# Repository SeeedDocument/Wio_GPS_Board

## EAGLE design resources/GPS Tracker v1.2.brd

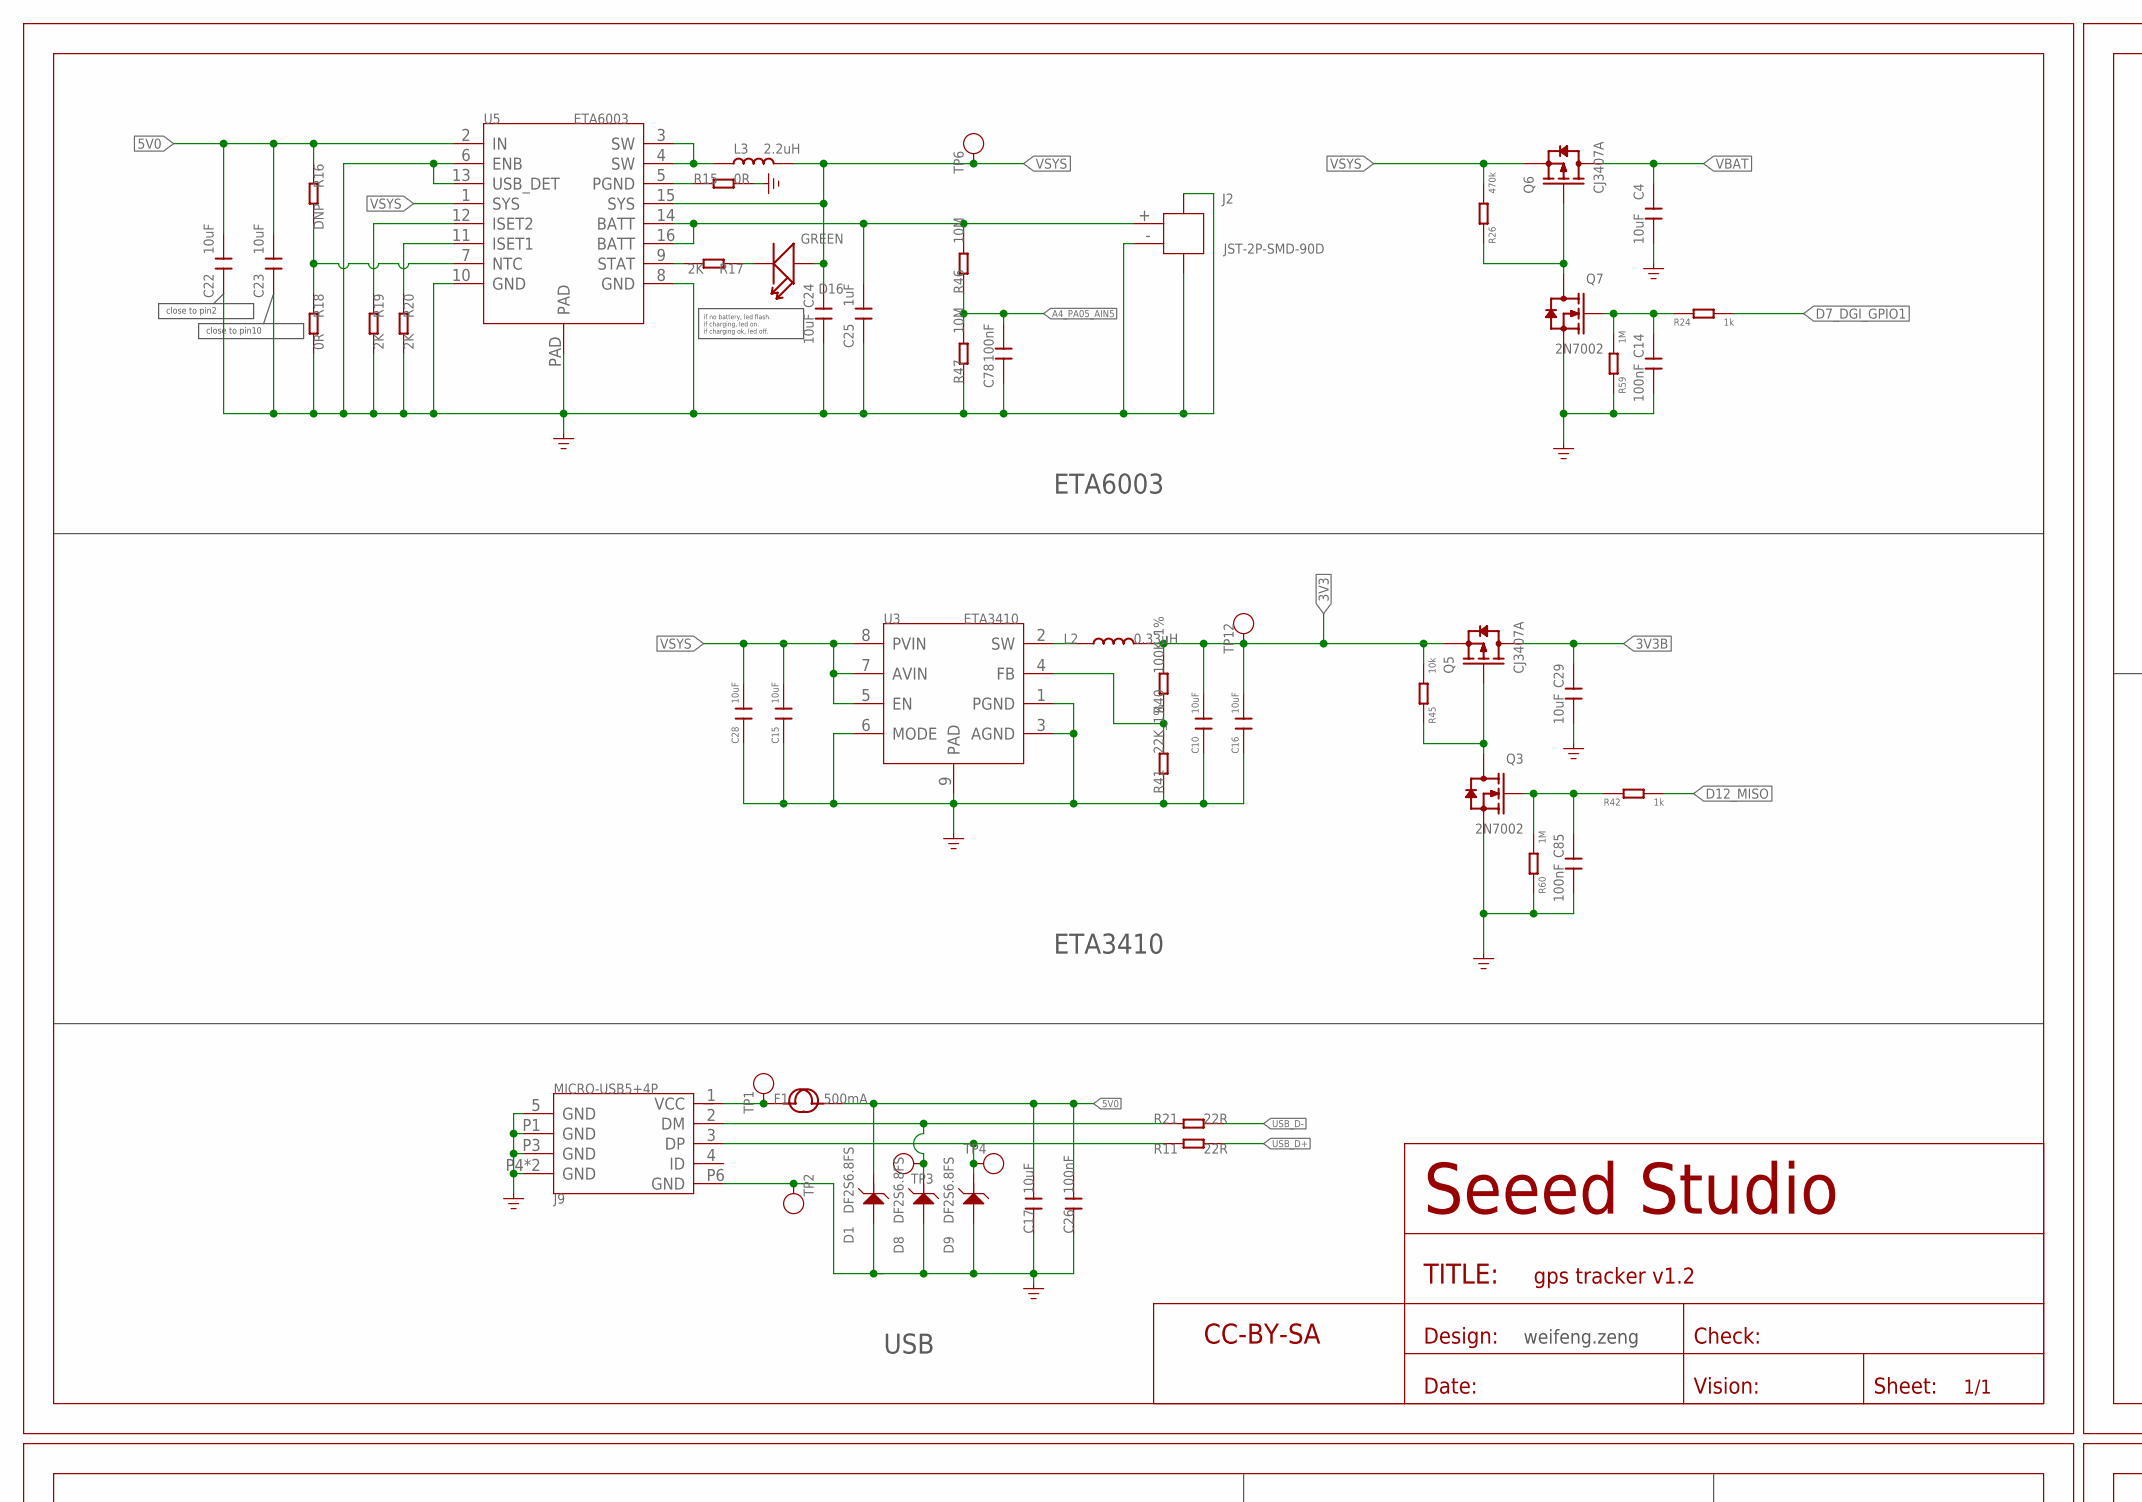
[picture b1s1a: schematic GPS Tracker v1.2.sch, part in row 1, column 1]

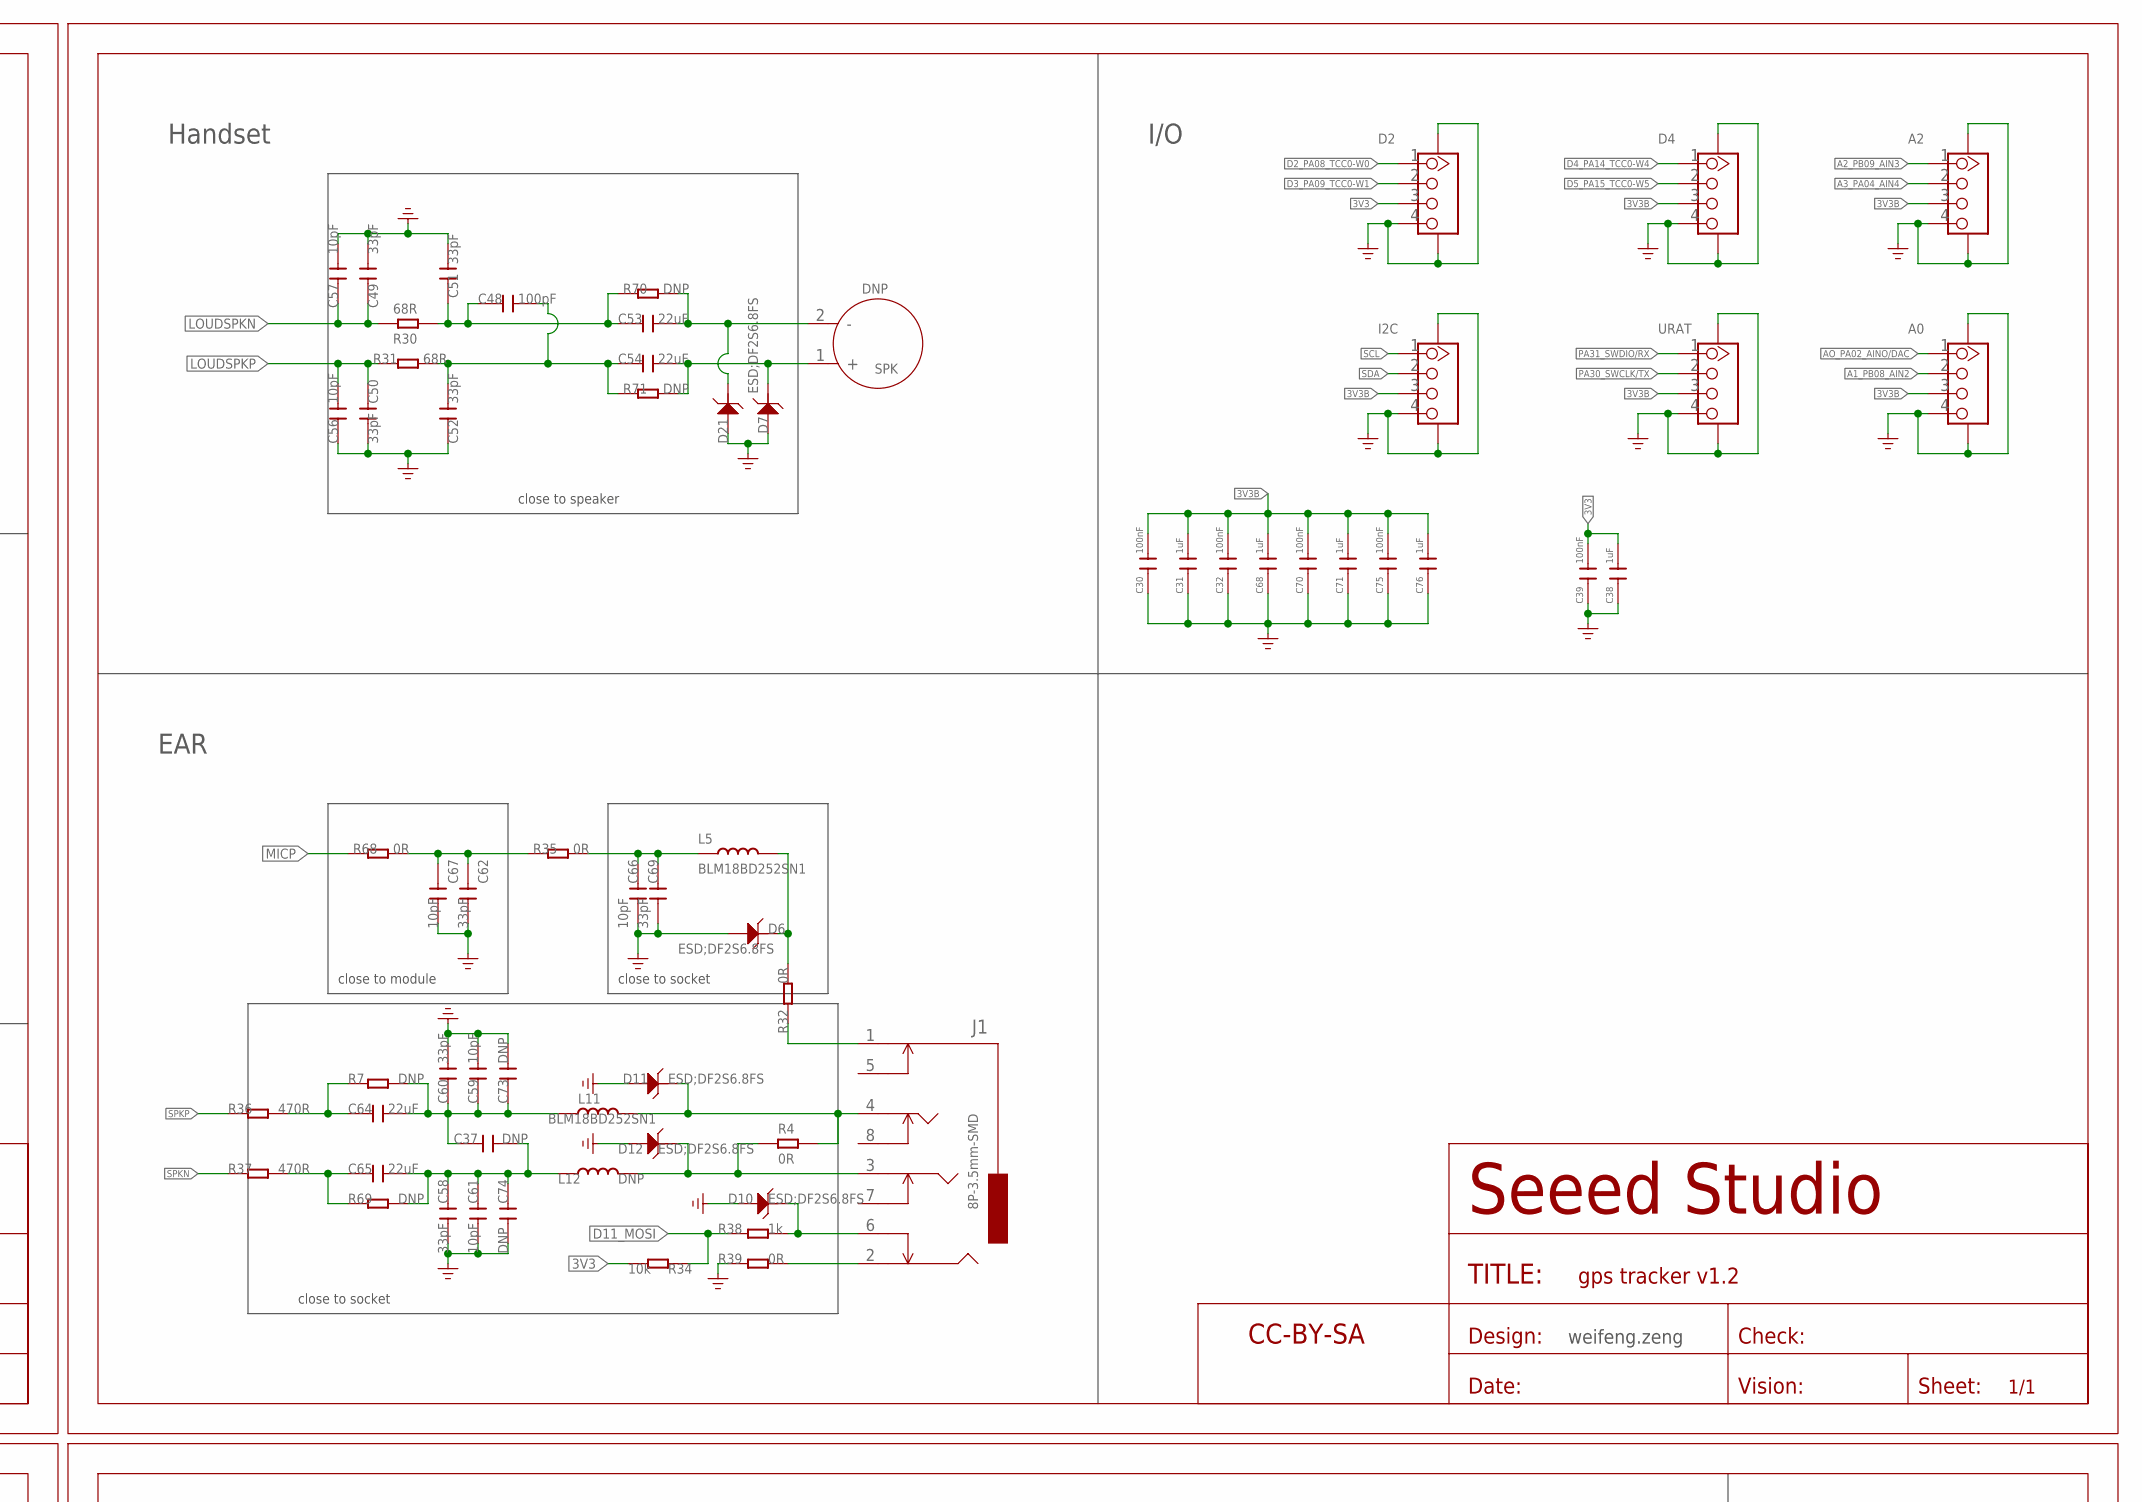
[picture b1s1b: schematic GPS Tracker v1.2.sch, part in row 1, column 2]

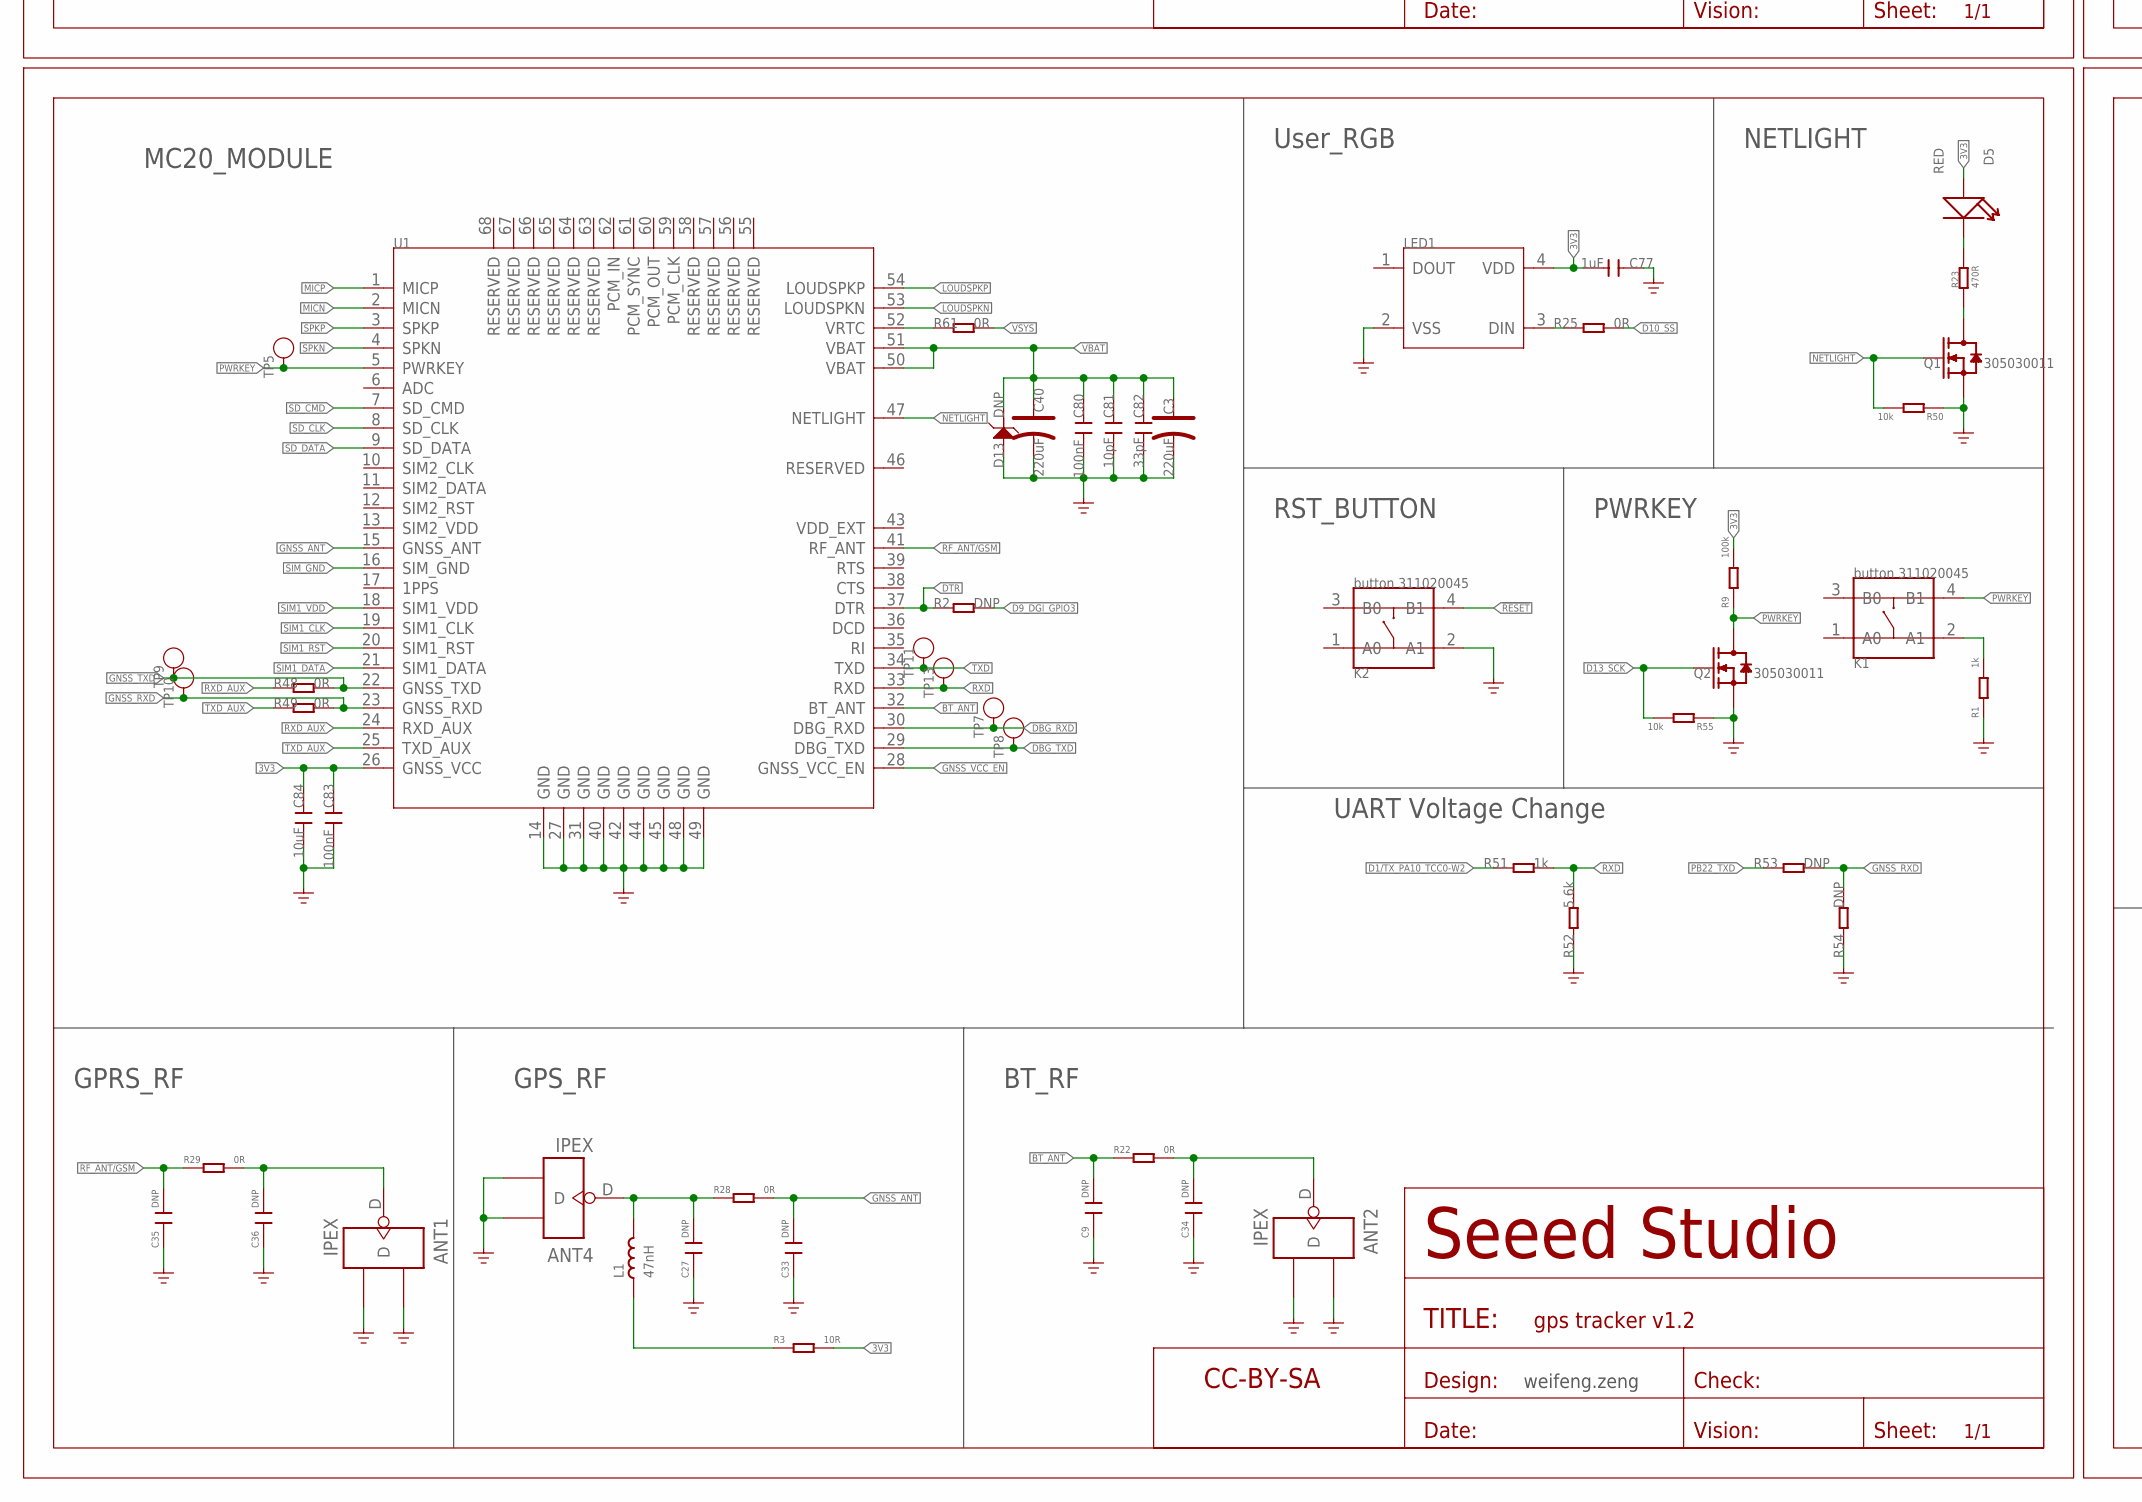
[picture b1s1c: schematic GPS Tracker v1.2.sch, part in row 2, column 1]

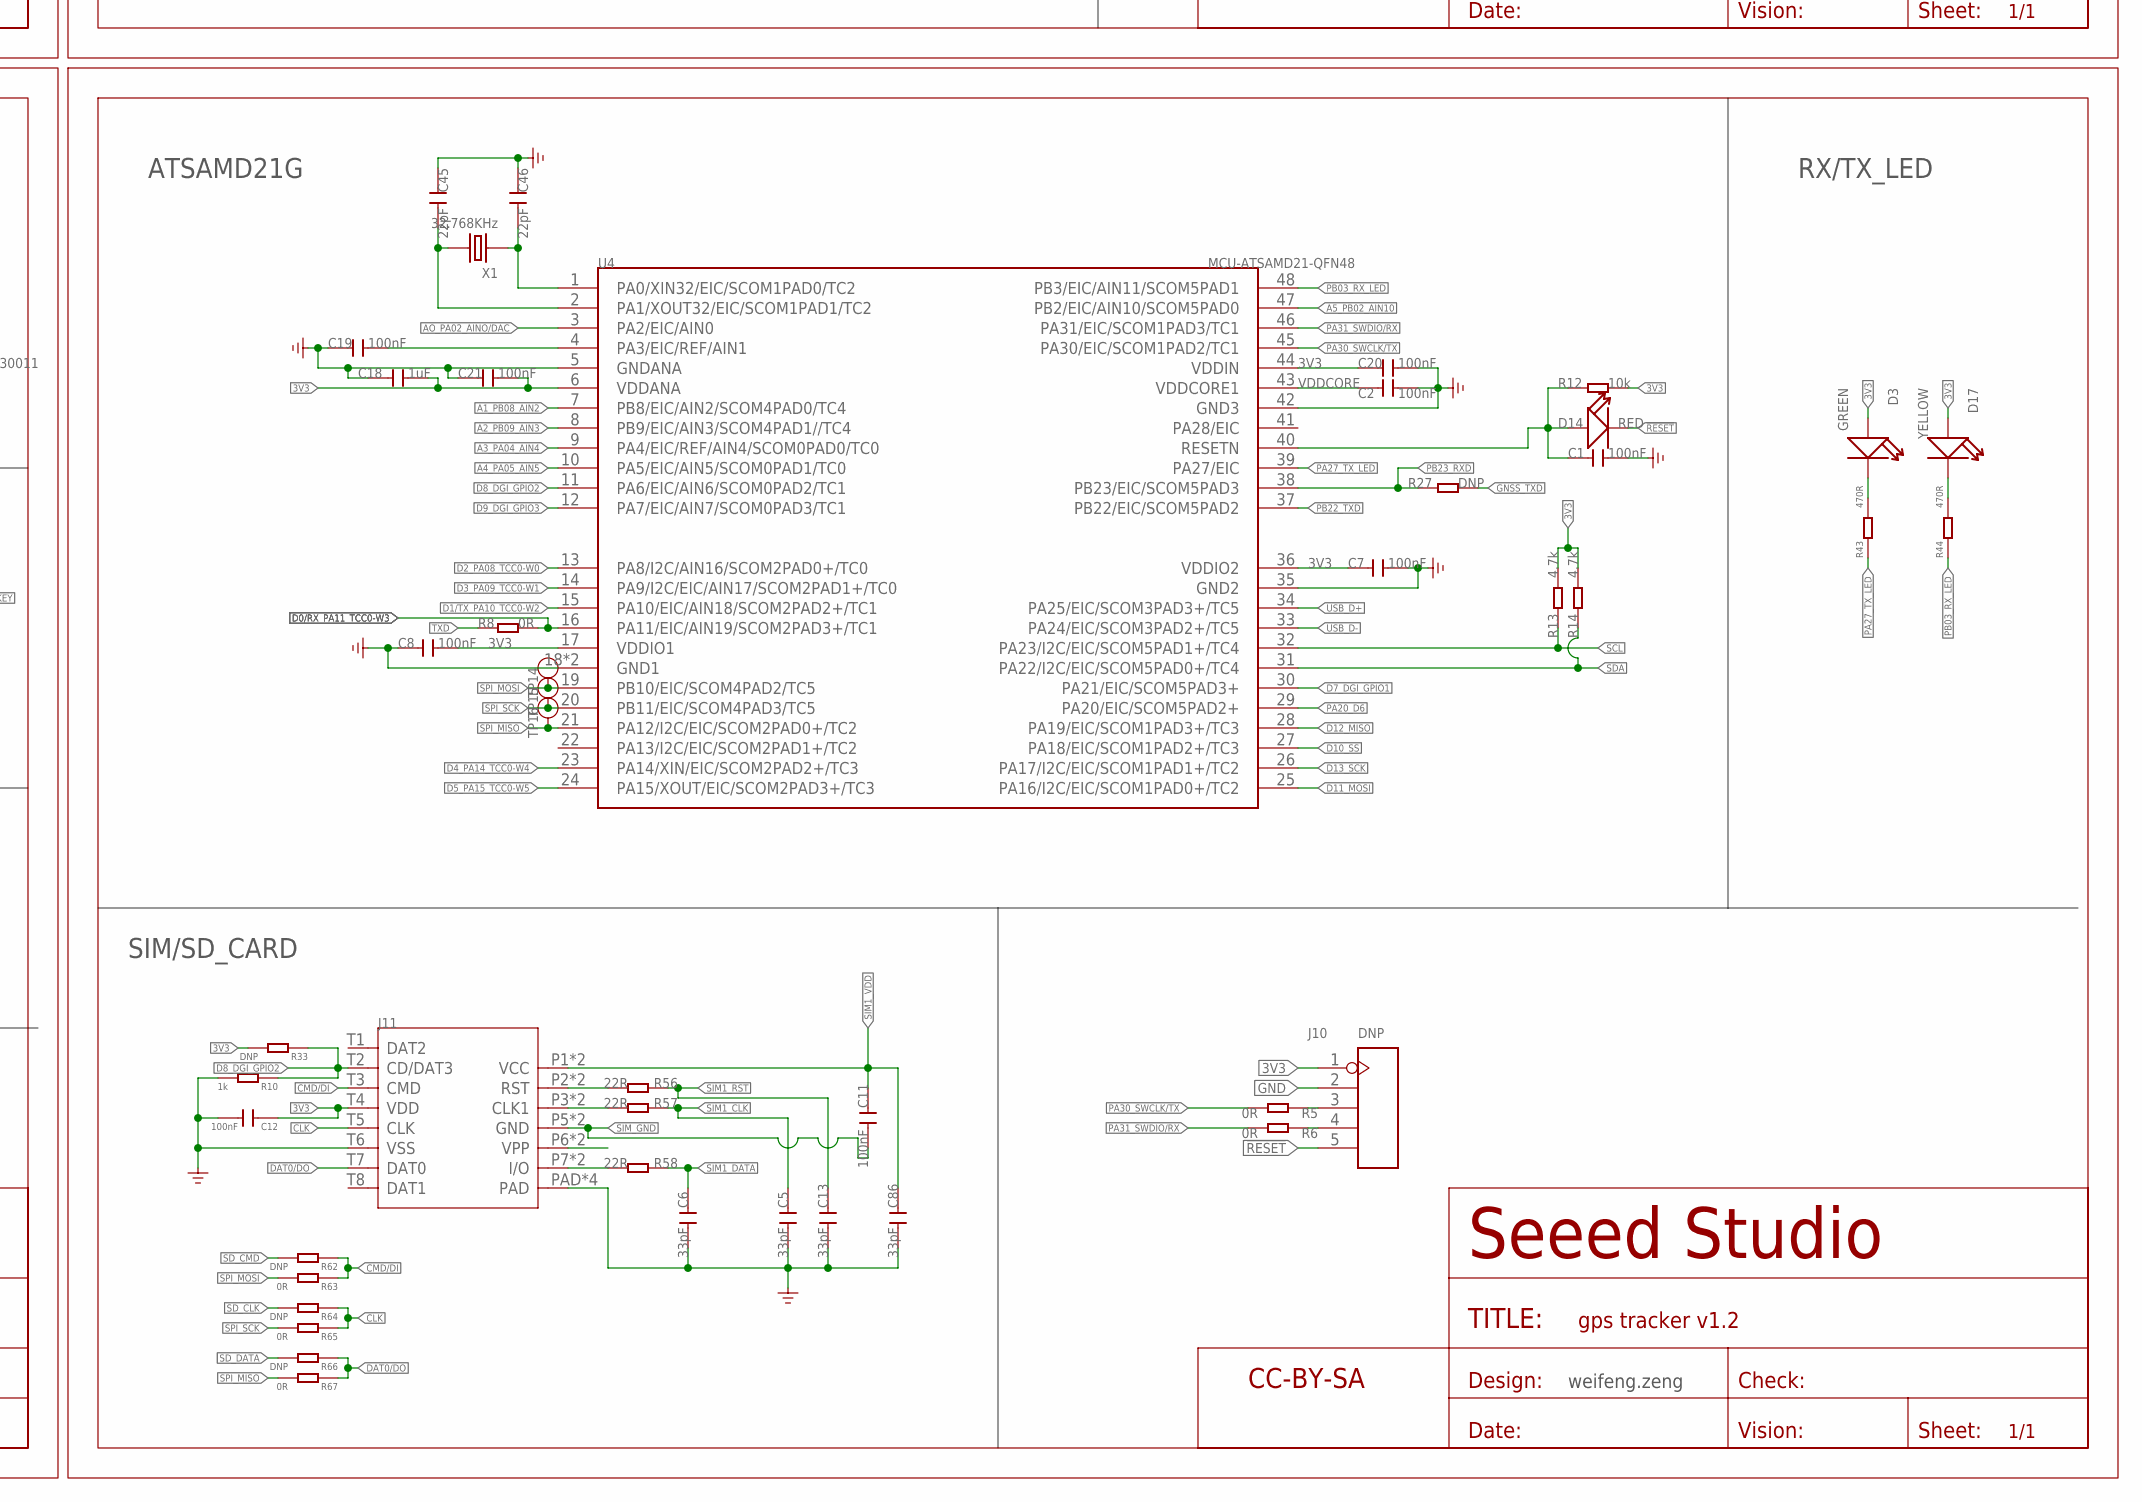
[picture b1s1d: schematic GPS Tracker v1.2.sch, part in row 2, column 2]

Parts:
A0, A2: GROVE-CONNECTOR-SMD'90D'; HW4-SMD-2.0-90D
ANT1, ANT2, ANT4: IPEX; U-FL3P-SMD-2.6X2.6X1.0MM
C1, C2, C7, C8, C11, C12, C19, C20, C21, C26, C30, C32, C39, C70, C75, C78, C80, C83: 100nF; C0402
C3, C40: 220uF; AVX-B
C4, C10, C15, C16, C17, C22, C23, C24, C28, C29, C84: 10uF; C0603
C5, C6, C13, C49, C50, C51, C52, C58, C60, C62, C69, C82, C86: 33pF; C0402
C9, C27, C33, C34, C35, C36, C37, C73, C74: DNP; C0402
C14, C85: 100nF; C0603
C18, C25, C31, C38, C68, C71, C76, C77: 1uF; C0402
C45, C46: 22pF; C0402
C48: 100pF; C0402
C53, C54, C64, C65: 22uF; C0805
C56, C57, C59, C61, C66, C67, C81: 10pF; C0402
D1, D8, D9: DF2S6.8FS; SOD-923
D2, D4: GROVE-CONNECTOR-SMD'90D'; HW4-SMD-2.0-90D
D3, D16: GREEN; LED-0402
D5, D14: RED; LED-0402
D6, D7, D10, D11, D12, D21: ESD;DF2S6.8FS; SOD-923
D13: DNP; SOD-923
D17: YELLOW; LED-0402
F1: 500mA; F1206
FR1, FR2, FR3, FR4: SEEEDSTUDIO-OPEN-SCH-FRAME; SEEEDSTUDIO-PCB-FRAME
I2C: GROVE-CONNECTOR-SMD'90D'; HW4-SMD-2.0-90D
J1: 8P-3.5mm-SMD; 8P-3.5-SMD
J2: JST-2P-SMD-90D; HW2-SMD-1.0-90D
J9: MICRO-USB5+4P; MICRO-USB5+5P-SMD-0.65-7.2X5.06MM
J10: DNP; H5-SMD-2.0-TEST
J11: NANO_SIM+TF-24P; SIM+TF-24P-SMD-1.2-15.05X13.66X2.5MM
K1, K2: button 311020045; SW4P-SMD-4.5X3.2X2.5MM
L1: 47nH; L0402
L2: 0.33uH; L201610
L3: 2.2uH; L0805
L5, L11: BLM18BD252SN1; L0603
L12: DNP; L0603
LED1: LED-RGB-4P-SK6812-SK6812; LED4-1.75-3.7X3.5X0.95MM
Q1, Q2: 305030011; SOT-323
Q3, Q7: 2N7002; SOT-23
Q5, Q6: CJ3407A; SOT-23
R1, R10, R24, R38, R42, R51: 1k; R0402
R2, R7, R16, R27, R33, R53, R54, R62, R64, R66, R69, R70, R71: DNP; R0402
R3: 10R; R0402
R4, R5, R6, R8, R15, R18, R22, R25, R28, R29, R32, R35, R39, R48, R49, R63, R65, R67, R68: 0R; R0402
R9: 100k; R0402
R11, R21, R56, R57, R58: 22R; R0402
R12, R34, R45, R50, R55: 10k; R0402
R13, R14: 4.7k; R0402
R17, R19, R20: 2K; R0402
R23, R36, R37, R43, R44: 470R; R0402
R26: 470k; R0402
R30, R31: 68R; R0402
R40: 100K_1%; R0402
R41: 22K_1%; R0402
R46, R47: 10M; R0402
R52: 5.6k; R0402
R59, R60: 1M; R0402
R61: 0R; R0603
SPK: DNP; 2P-SMD-SPEAKER
TP1, TP2, TP3, TP4, TP5, TP6, TP7, TP8, TP9, TP10, TP11, TP12, TP13, TP14, TP15, TP16: TEST-POINT'4545'; TP-D45MIL
U1: MODULE-MC20; MODULE68P-SMD-1.0-18.7X16X2.1MM
U3: ETA3410; DFN8G-0.5-2X2MM
U4: MCU-ATSAMD21-QFN48; QFN48-7X7
U5: ETA6003; QFN16G-0.5-3X3MM@1
URAT: GROVE-CONNECTOR-SMD'90D'; HW4-SMD-2.0-90D
X1: 32.768KHz; X2-SMD-L2.0X1.2X0.55MM

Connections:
3V3: C7.1, C8.2, C10.2, C12.1, C16.2, C18.2, C20.1, C21.2, C38.2, C39.2, C77.2, C83.2, C84.2, D2.3, D3.+, D5.+, D17.+, J10.1, J11.T4 (VDD), L2.2, LED1.4 (VDD), Q5.2 (S), R3.2, R9.2, R12.1, R13.2, R14.2, R33.2, R34.1, R40.2, R45.2, TP12.T, U1.26 (GNSS_VCC), U4.6 (VDDANA), U4.17 (VDDIO1), U4.36 (VDDIO2), U4.44 (VDDIN)
3V3B: A0.3, A2.3, C29.1, C30.2, C31.2, C32.2, C68.2, C70.2, C71.2, C75.2, C76.2, D4.3, I2C.3, Q5.3 (D), URAT.3
5V0: C17.1, C22.1, C23.1, C26.1, D1.1 (2), F1.2, R16.1, U5.2 (IN)
!RESET: D14.-, J10.5, K2.4 (B1)
A1_PB08_AIN2: A0.2, U4.7 (PB8/EIC/AIN2/SCOM4PAD0/TC4)
A2_PB09_AIN3: A2.1, U4.8 (PB9/EIC/AIN3/SCOM4PAD1//TC4)
A3_PA04_AIN4: A2.2, U4.9 (PA4/EIC/REF/AIN4/SCOM0PAD0/TC0)
A4_PA05_AIN5: C78.1, R46.1, R47.2, U4.10 (PA5/EIC/AIN5/SCOM0PAD1/TC0)
A5_PB02_AIN10: U4.47 (PB2/EIC/AIN10/SCOM5PAD0)
AO_PA02_AINO/DAC: A0.1, U4.3 (PA2/EIC/AIN0)
BT_ANT: C9.2, R22.1, U1.32 (BT_ANT)
CLK: J11.T5 (CLK), R64.1, R65.1
CMD/DI: J11.T3 (CMD), R62.1, R63.1
D0/RX_PA11_TCC0-W3: R8.2, U4.16 (PA11/EIC/AIN19/SCOM2PAD3+/TC1)
D1/TX_PA10_TCC0-W2: R51.1, U4.15 (PA10/EIC/AIN18/SCOM2PAD2+/TC1)
D2_PA08_TCC0-W0: D2.1, U4.13 (PA8/I2C/AIN16/SCOM2PAD0+/TC0)
D3_PA09_TCC0-W1: D2.2, U4.14 (PA9/I2C/EIC/AIN17/SCOM2PAD1+/TC0)
D4_PA14_TCC0-W4: D4.1, U4.23 (PA14/XIN/EIC/SCOM2PAD2+/TC3)
D5_PA15_TCC0-W5: D4.2, U4.24 (PA15/XOUT/EIC/SCOM2PAD3+/TC3)
D7_DGI_GPIO1: R24.2, U4.30 (PA21/EIC/SCOM5PAD3+)
D8_DGI_GPIO2: J11.T2 (CD/DAT3), R10.1, R33.1, U4.11 (PA6/EIC/AIN6/SCOM0PAD2/TC1)
D9_DGI_GPIO3: R2.2, U4.12 (PA7/EIC/AIN7/SCOM0PAD3/TC1)
D10_SS: R25.2, U4.27 (PA18/EIC/SCOM1PAD2+/TC3)
D11_MOSI: R34.2, R38.1, U4.25 (PA16/I2C/EIC/SCOM1PAD0+/TC2)
D12_MISO: R42.2, U4.28 (PA19/EIC/SCOM1PAD3+/TC3)
D13_SCK: Q2.1 (G), R55.2, U4.26 (PA17/I2C/EIC/SCOM1PAD1+/TC2)
D-1: D8.1 (2), J9.2 (DM), R21.1, TP3.T
DAT0/DO: J11.T7 (DAT0), R66.1, R67.1
DBG_RXD: TP7.T, U1.30 (DBG_RXD)
DBG_TXD: TP8.T, U1.29 (DBG_TXD)
DTR: R2.1, U1.37 (DTR)
FM_N: D12.1 (2), J1.3, L12.2, R4.1
FM_P: D11.1 (2), J1.4, L11.2, R4.2
GND: A0.4, A0.SS1, A0.SS2, A2.4, A2.SS1, A2.SS2, ANT1.GND1, ANT1.GND2, ANT2.GND1, ANT2.GND2, ANT4.GND1, ANT4.GND2, C1.2, C2.2, C3.-, C4.2, C5.1, C6.1, C7.2, C8.1, C9.1, C10.1, C12.2, C13.1, C14.2, C15.1, C16.1, C17.2, C18.1, C19.1, C20.2, C21.1, C22.2, C23.2, C24.2, C25.2, C26.2, C27.1, C28.1, C29.2, C30.1, C31.1, C32.1, C33.1, C34.1, C35.1, C36.1, C38.1, C39.1, C40.-, C45.1, C46.1, C49.1, C50.1, C51.1, C52.1, C56.1, C57.1, C58.1, C59.2, C60.1, C61.1, C62.1, C66.1, C67.1, C68.1, C69.1, C70.1, C71.1, C73.2, C74.1, C75.1, C76.1, C77.1, C78.2, C80.1, C81.1, C82.1, C83.1, C84.1, C85.2, C86.1, D1.2 (1), D2.4, D2.SS1, D2.SS2, D4.4, D4.SS1, D4.SS2, D6.2 (1), D7.2 (1), D8.2 (1), D9.2 (1), D10.2 (1), D11.2 (1), D12.2 (1), D13.2 (1), D21.2 (1), I2C.4, I2C.SS1, I2C.SS2, J2.3, J2.4, J2.- (2), J9.5 (GND), J9.P1 (GND), J9.P3 (GND), J9.P4 (GND), J9.P5 (GND), J9.P6 (GND), J10.2, J11.PAD, J11.PAD1 (PAD), J11.PAD2 (PAD), J11.PAD3 (PAD), J11.T6 (VSS), K2.2 (A1), LED1.2 (VSS), Q1.2 (S), Q2.2 (S), Q3.2 (S), Q7.2 (S), R1.1, R10.2, R15.2, R18.2, R19.2, R20.2, R39.1, R41.1, R47.1, R50.1, R52.1, R54.1, R55.1, R59.1, R60.1, TP2.T, U1.14 (GND), U1.27 (GND), U1.31 (GND), U1.40 (GND), U1.42 (GND), U1.44 (GND), U1.45 (GND), U1.48 (GND), U1.49 (GND), U3.1 (PGND), U3.3 (AGND), U3.6 (MODE), U3.9 (PAD), U4.5 (GNDANA), U4.18 (GND1), U4.35 (GND2), U4.42 (GND3), U4.PAD (GND1), U5.6 (ENB), U5.8 (GND), U5.10 (GND), U5.13 (USB_DET), U5.PAD, URAT.4, URAT.SS1, URAT.SS2
GNSS_ANT: C33.2, R28.2, U1.15 (GNSS_ANT)
GNSS_RXD: R49.2, R53.2, R54.2, TP10.T, U1.23 (GNSS_RXD)
GNSS_TXD: R27.1, R48.2, TP9.T, U1.22 (GNSS_TXD)
GNSS_VCC_EN: U1.28 (GNSS_VCC_EN)
LOUDSPKN: C49.2, C57.2, R30.1, U1.53 (LOUDSPKN)
LOUDSPKP: C50.2, C56.2, R31.1, U1.54 (LOUDSPKP)
MICN: U1.2 (MICN)
MICP: R68.1, U1.1 (MICP)
unnamed: Q6.1 (G), Q7.3 (D), R26.1
unnamed: LED1.3 (DIN), R25.1
unnamed: K1.2 (A1), R1.2
unnamed: L1.1, R3.1
unnamed: C19.2, U4.4 (PA3/EIC/REF/AIN1)
unnamed: J1.1, R32.1
unnamed: C14.1, Q7.1 (G), R24.1, R59.2
unnamed: C46.2, U4.1 (PA0/XIN32/EIC/SCOM1PAD0/TC2), X1.1
unnamed: ANT2.D, C34.2, R22.2
unnamed: R61.1, U1.52 (VRTC)
unnamed: C1.1, D14.+, R12.2, U4.40 (RESETN)
unnamed: ANT4.D, C27.2, L1.2, R28.1
unnamed: ANT1.D, C36.2, R29.2
unnamed: R40.1, R41.2, U3.4 (FB)
unnamed: C53.2, D21.1 (2), R70.2, SPK.2 (-)
unnamed: Q1.3 (D), R23.1
unnamed: D5.-, R23.2
unnamed: L3.1, U5.3 (SW), U5.4 (SW)
unnamed: Q3.3 (D), Q5.1 (G), R45.1
unnamed: C25.1, J2.+ (1), R46.2, U5.14 (BATT), U5.16 (BATT)
unnamed: L2.1, U3.2 (SW)
unnamed: D16.-, R17.1
unnamed: R17.2, U5.9 (STAT)
unnamed: C54.2, D7.1 (2), R71.2, SPK.1 (+)
unnamed: R16.2, R18.1, U5.7 (NTC)
unnamed: R20.1, U5.11 (ISET1)
unnamed: R19.1, U5.12 (ISET2)
unnamed: R15.1, U5.5 (PGND)
unnamed: C48.1, C51.2, C53.1, R30.2, R70.1
unnamed: C48.2, C52.2, C54.1, R31.2, R71.1
unnamed: D6.1 (2), L5.2, R32.2
unnamed: C62.2, C67.2, R35.1, R68.2
unnamed: D9.1 (2), J9.3 (DP), R11.1, TP4.T
unnamed: D10.1 (2), J1.6, R38.2
unnamed: J10.3, R5.1
unnamed: J10.4, R6.1
unnamed: C45.2, U4.2 (PA1/XOUT32/EIC/SCOM1PAD1/TC2), X1.2
unnamed: J1.2, R39.2
unnamed: F1.1, J9.1 (VCC), TP1.T
unnamed: C66.2, C69.2, L5.1, R35.2
unnamed: C37.2, C58.2, C61.2, C65.2, C74.2, L12.1, R69.2
unnamed: C65.1, R37.2, R69.1
unnamed: C64.1, R7.1, R36.2
unnamed: C37.1, C59.1, C60.2, C64.2, C73.1, L11.1, R7.2
unnamed: C85.1, Q3.1 (G), R42.1, R60.2
unnamed: D3.-, R43.2
unnamed: D17.-, R44.2
unnamed: J11.P2 (RST), J11.P2B (RST), R56.2
unnamed: J11.P3 (CLK1), J11.P3B (CLK1), R57.2
unnamed: J11.P6 (VPP), J11.P6B (VPP)
unnamed: J11.P7 (I/O), J11.P7B (I/O), R58.2
NETLIGHT: Q1.1 (G), R50.2, U1.47 (NETLIGHT)
PA20_D6: U4.29 (PA20/EIC/SCOM5PAD2+)
PA27_TX_LED: R43.1, U4.39 (PA27/EIC)
PA30_SWCLK/TX: R5.2, U4.45 (PA30/EIC/SCOM1PAD2/TC1), URAT.2
PA31_SWDIO/RX: R6.2, U4.46 (PA31/EIC/SCOM1PAD3/TC1), URAT.1
PB03_RX_LED: R44.1, U4.48 (PB3/EIC/AIN11/SCOM5PAD1)
PB22_TXD: R53.1, U4.37 (PB22/EIC/SCOM5PAD2)
PB23_RXD: R27.2, U4.38 (PB23/EIC/SCOM5PAD3)
PWRKEY: K1.4 (B1), Q2.3 (D), R9.1, TP5.T, U1.5 (PWRKEY)
RF_ANT/GSM: C35.2, R29.1, U1.41 (RF_ANT)
RXD: R51.2, R52.2, TP13.T, U1.33 (RXD)
RXD_AUX: R48.1, U1.24 (RXD_AUX)
SCL: I2C.1, R13.1, U4.32 (PA23/I2C/EIC/SCOM5PAD1+/TC4)
SDA: I2C.2, R14.1, U4.31 (PA22/I2C/EIC/SCOM5PAD0+/TC4)
SD_CLK: R64.2, U1.8 (SD_CLK)
SD_CMD: R62.2, U1.7 (SD_CMD)
SD_DATA: R66.2, U1.9 (SD_DATA)
SIM1_CLK: C5.2, R57.1, U1.19 (SIM1_CLK)
SIM1_DATA: C6.2, R58.1, U1.21 (SIM1_DATA)
SIM1_RST: C13.2, R56.1, U1.20 (SIM1_RST)
SIM1_VDD: C11.2, C86.2, J11.P1 (VCC), J11.P1B (VCC), U1.18 (SIM1_VDD)
SIM_GND: C11.1, J11.P5 (GND), J11.P5B (GND), U1.16 (SIM_GND)
SPI_MISO: R67.2, TP16.T, U4.21 (PA12/I2C/EIC/SCOM2PAD0+/TC2)
SPI_MOSI: R63.2, TP14.T, U4.19 (PB10/EIC/SCOM4PAD2/TC5)
SPI_SCK: R65.2, TP15.T, U4.20 (PB11/EIC/SCOM4PAD3/TC5)
SPKN: R37.1, U1.4 (SPKN)
SPKP: R36.1, U1.3 (SPKP)
TXD: R8.1, TP11.T, U1.34 (TXD)
TXD_AUX: R49.1, U1.25 (TXD_AUX)
USB_D+: R11.2, U4.34 (PA25/EIC/SCOM3PAD3+/TC5)
USB_D-: R21.2, U4.33 (PA24/EIC/SCOM3PAD2+/TC5)
VBAT: C3.+, C4.1, C40.+, C80.2, C81.2, C82.2, D13.1 (2), Q6.3 (D), U1.50 (VBAT), U1.51 (VBAT)
VDDCORE: C2.1, U4.43 (VDDCORE1)
VSYS: C15.2, C24.1, C28.2, D16.+, L3.2, Q6.2 (S), R26.2, R61.2, TP6.T, U3.5 (EN), U3.7 (AVIN), U3.8 (PVIN), U5.1 (SYS), U5.15 (SYS)

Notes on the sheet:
close to pin10
if no battery, led flash. if charging, led on. if charging ok, led off.
close to pin2
ETA6003
ETA3410
USB
Handset
EAR
NETLIGHT
RST_BUTTON
GPS_RF
GPRS_RF
ATSAMD21G
User_RGB
I/O
RX/TX_LED
weifeng.zeng
BT_RF
MC20_MODULE
close to module
close to socket
close to speaker
UART Voltage Change
PWRKEY
SIM/SD_CARD

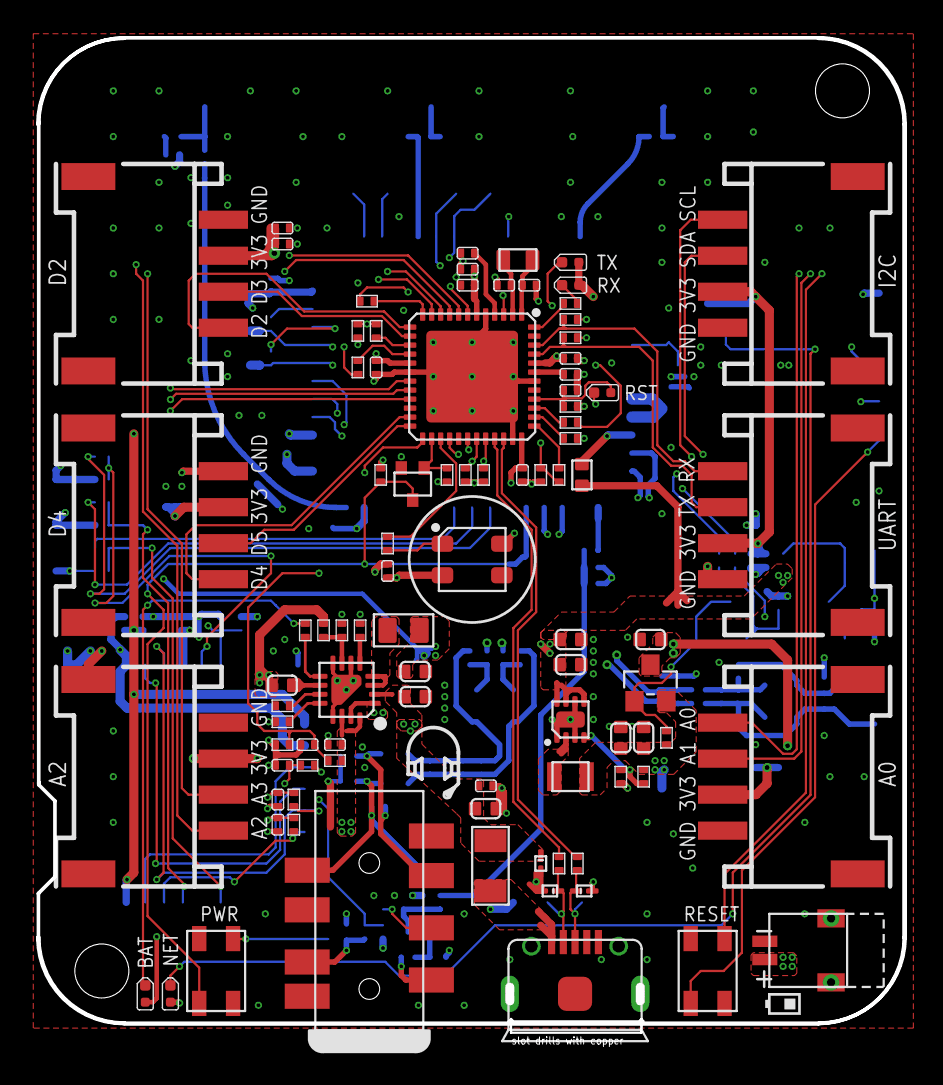
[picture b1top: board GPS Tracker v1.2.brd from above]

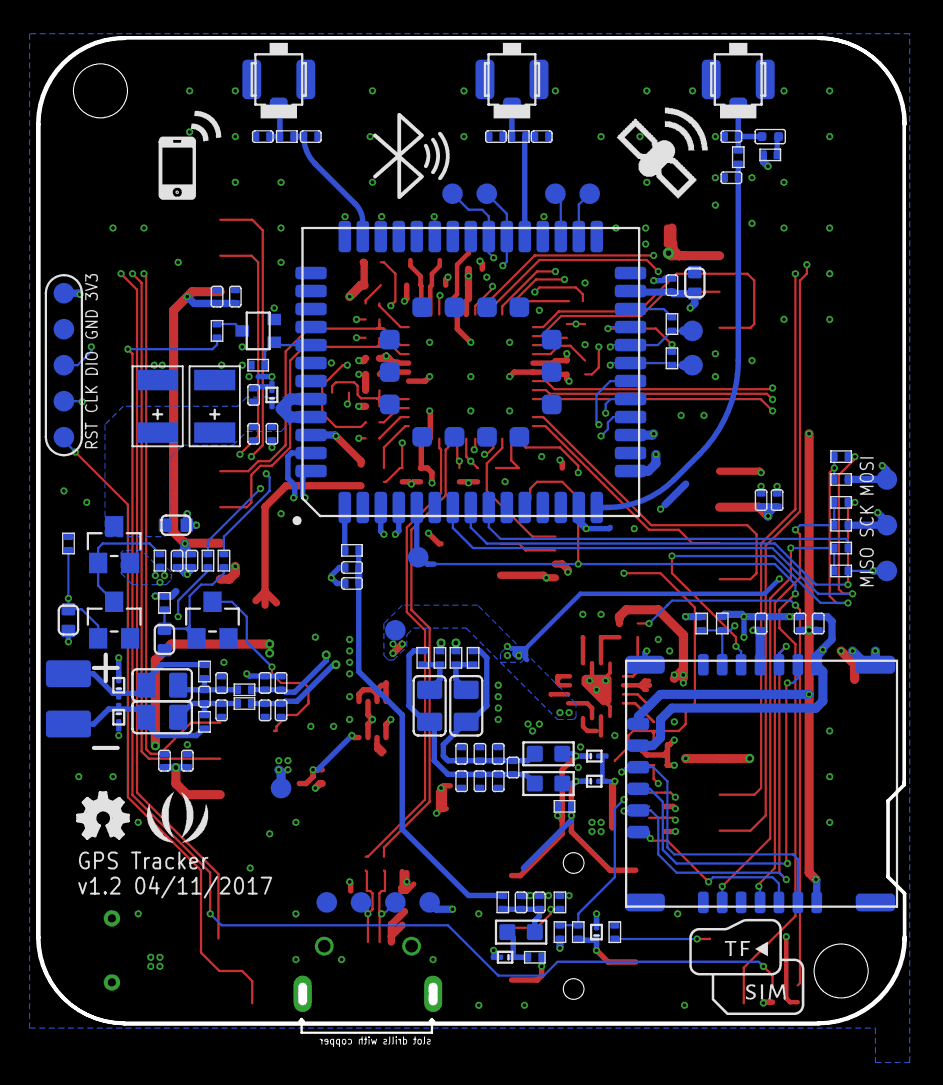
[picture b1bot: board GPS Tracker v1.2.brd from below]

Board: 4 copper layers, 48.2 x 55.3 mm, 221 parts (126 on the bottom side), 123 nets.

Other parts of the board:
U$10: OSHW_FILLX100_NOTEXT
U$14: SEEED-SILK--TNAME-160*153MIL

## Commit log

2017-04-14 add images and files
2017-04-17 wiki v0.9
2017-04-20 change name
2017-04-25 add demo code
2017-04-28 fixed the format error
2017-06-15 add setup pictures and new eagle files

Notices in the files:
parts and their libraries:
moudle-new: This work is licensed under the Creative Commons Attribution 4.0 International License.
To view a copy of this license,visit:
http://creativecommons.org/licenses/by-sa/4.0
moudle-new: CC-BY-SA
